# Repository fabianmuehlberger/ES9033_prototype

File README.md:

# ES9033_prototype
prototype board with ES9033 DAC

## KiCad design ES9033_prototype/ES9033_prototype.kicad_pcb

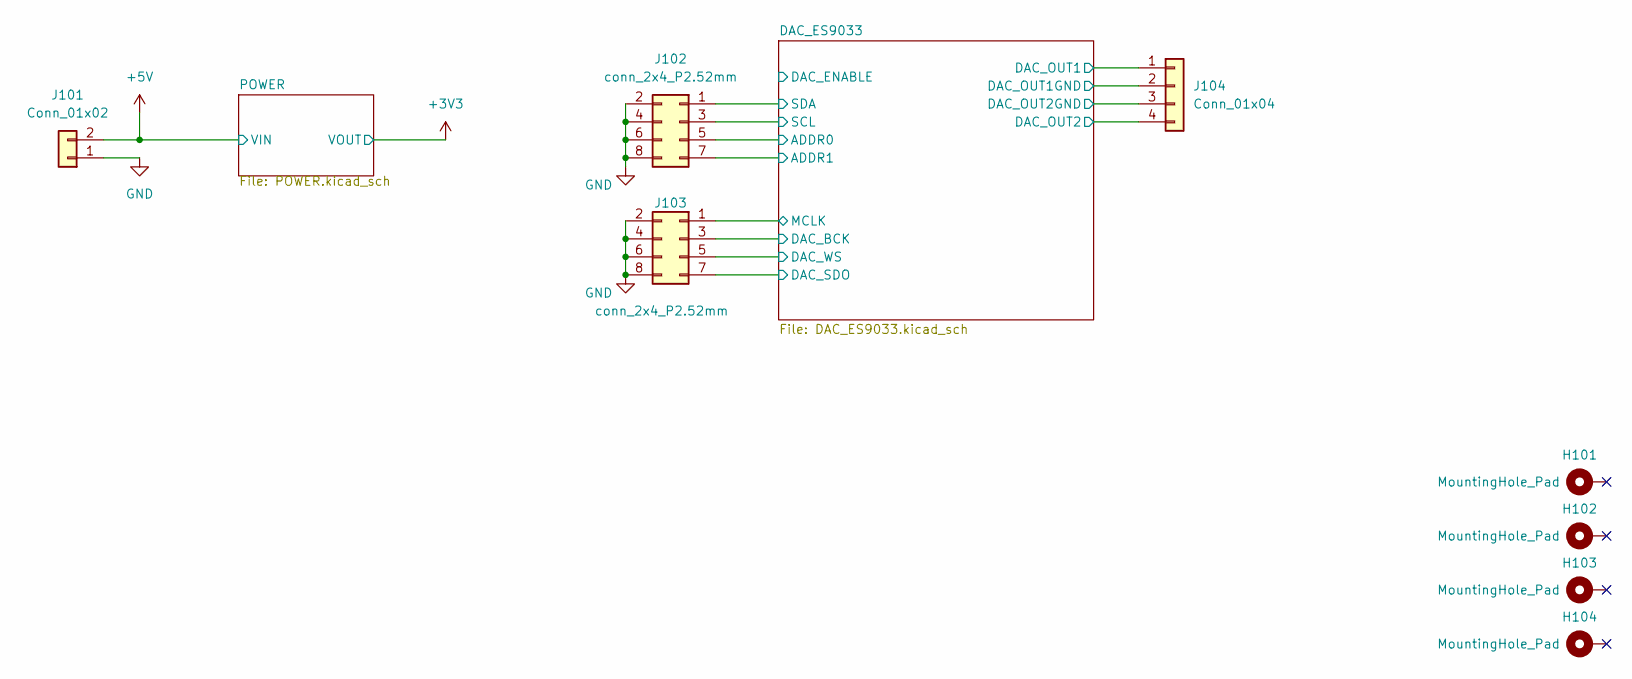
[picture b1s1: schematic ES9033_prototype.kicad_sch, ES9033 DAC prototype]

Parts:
H101, H102, H103, H104: MountingHole_Pad; MountingHole_3.2mm_M3_DIN965_Pad
J101: Conn_01x02; PinHeader_1x02_P2.54mm_Vertical
J102, J103: conn_2x4_P2.52mm; PinHeader_2x04_P2.54mm_Vertical
J104: Conn_01x04; PinHeader_1x04_P2.54mm_Vertical

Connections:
+5V: J101.2; also elsewhere on the board
/DAC_ES9033/ADDR0: J102.5; also elsewhere on the board
/DAC_ES9033/ADDR1: J102.7; also elsewhere on the board
/DAC_ES9033/DAC_BCK: J103.3; also elsewhere on the board
/DAC_ES9033/DAC_OUT1: J104.1; also elsewhere on the board
/DAC_ES9033/DAC_OUT2: J104.4; also elsewhere on the board
/DAC_ES9033/DAC_SDO: J103.7; also elsewhere on the board
/DAC_ES9033/DAC_WS: J103.5; also elsewhere on the board
/DAC_ES9033/MCLK: J103.1; also elsewhere on the board
/DAC_ES9033/SCL: J102.3; also elsewhere on the board
/DAC_ES9033/SDA: J102.1; also elsewhere on the board
GND: J101.1, J102.2, J102.4, J102.6, J102.8, J103.2, J103.4, J103.6, J103.8, J104.2, J104.3; also elsewhere on the board

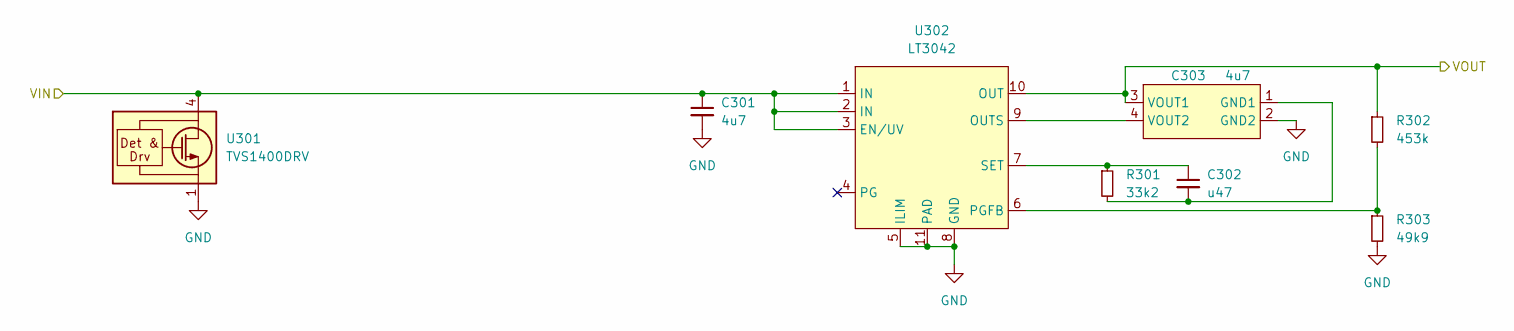
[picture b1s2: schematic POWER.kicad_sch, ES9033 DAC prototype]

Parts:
C301: 4u7; C_1206_3216Metric
C302: u47; C_1206_3216Metric
C303: 4u7; 1206_split
R301: 33k2; R_0805_2012Metric
R302: 453k; R_0805_2012Metric
R303: 49k9; R_0805_2012Metric
U301: TVS1400DRV; WSON-6-1EP_2x2mm_P0.65mm_EP1x1.6mm
U302: LT3042; DFN-10-1EP_3x3mm_P0.5mm_EP1.7x2.5mm

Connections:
+3V3: C303.3 (VOUT1), R302.1, U302.10 (OUT); also elsewhere on the board
+5V: C301.1, U301.4 (IN), U301.5 (IN), U301.6 (IN), U302.1 (IN), U302.2 (IN), U302.3 (EN/UV); also elsewhere on the board
GND: C301.2, C303.2 (GND2), R303.2, U301.1 (GND), U301.2 (GND), U301.3 (GND), U301.7 (GND), U302.5 (ILIM), U302.8 (GND), U302.11 (PAD); also elsewhere on the board
unnamed: C302.1, R301.1, U302.7 (SET)
unnamed: C302.2, C303.1 (GND1), R301.2
unnamed: C303.4 (VOUT2), U302.9 (OUTS)
unnamed: R302.2, R303.1, U302.6 (PGFB)

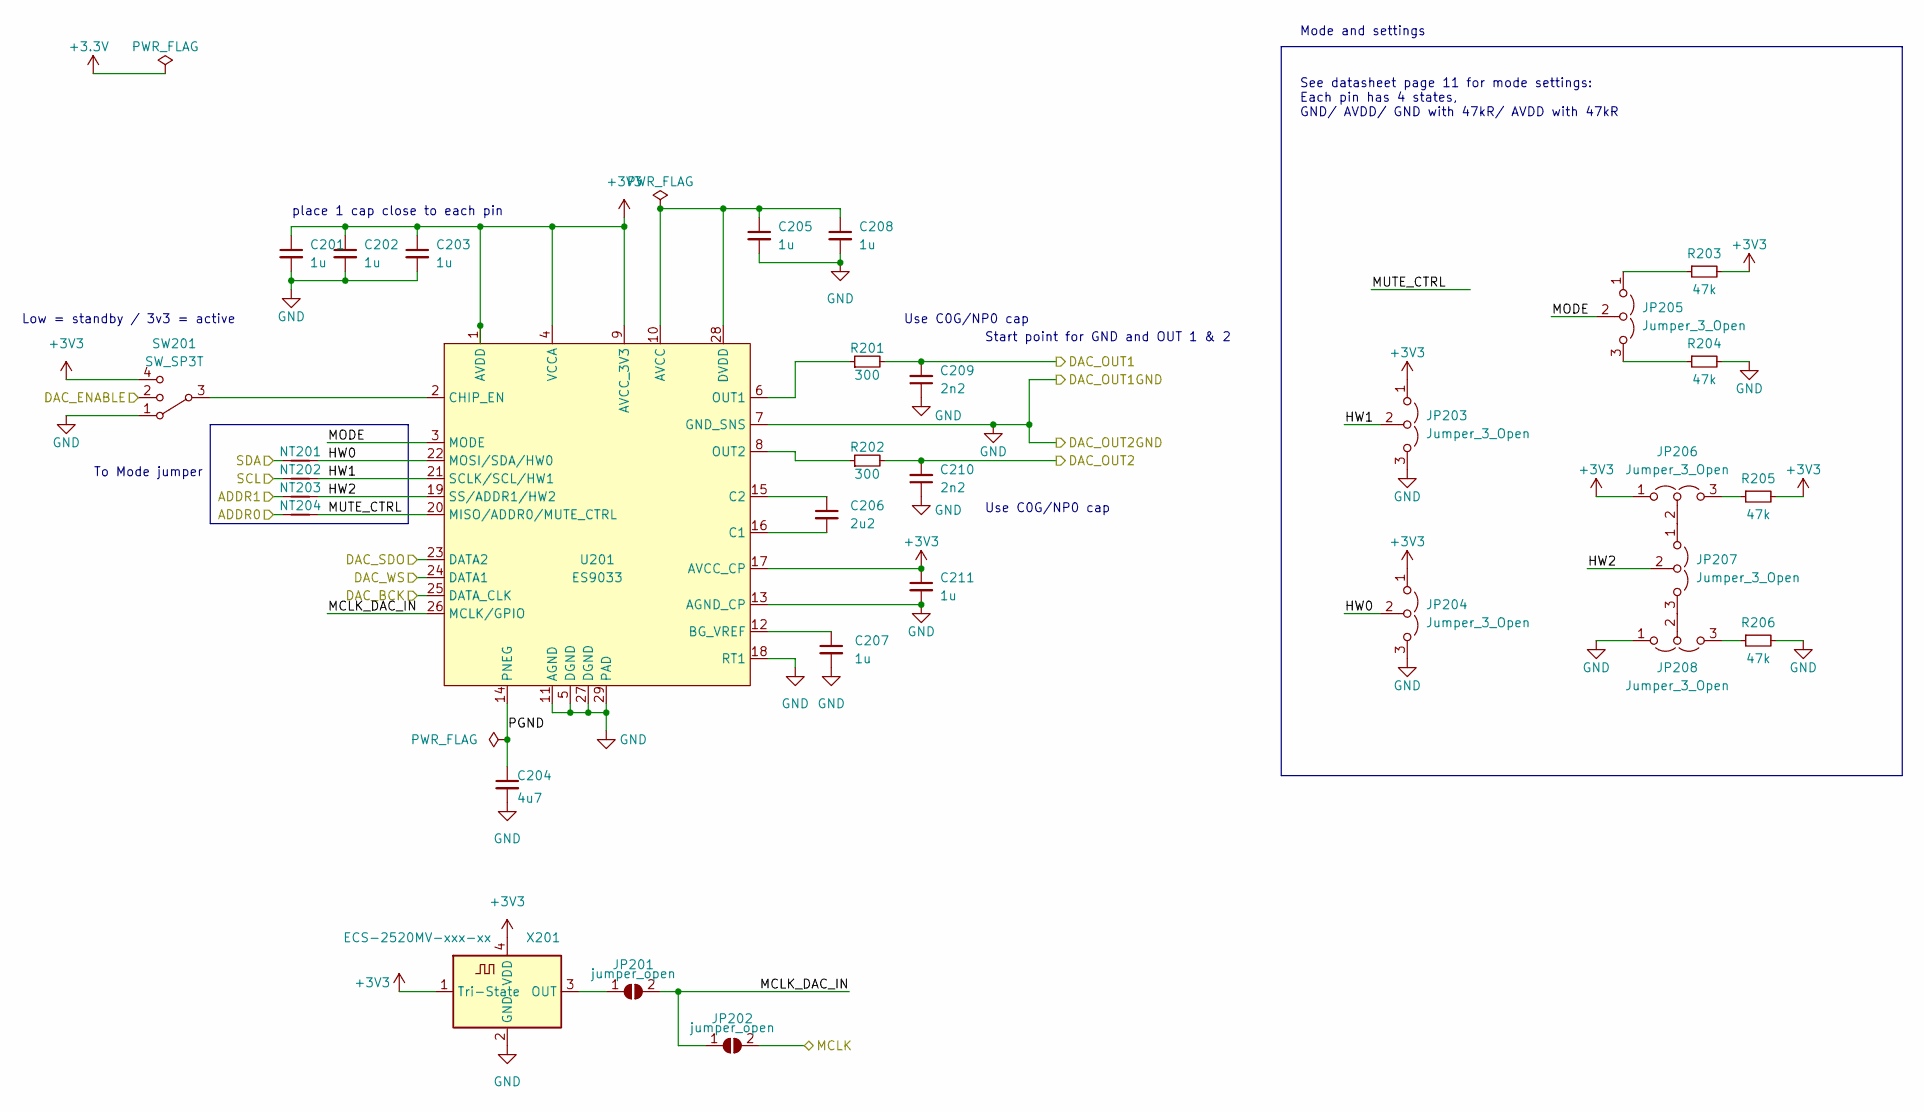
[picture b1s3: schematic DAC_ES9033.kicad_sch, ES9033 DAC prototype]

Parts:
C201, C202, C203, C205, C207, C208, C211: 1u; C_0805_2012Metric
C204: 4u7; C_0805_2012Metric
C206: 2u2; C_0805_2012Metric
C209, C210: 2n2; C_0805_2012Metric
JP201, JP202: jumper_open; SolderJumper-2_P1.3mm_Open_Pad1.0x1.5mm
JP203, JP204, JP205, JP206, JP207, JP208: Jumper_3_Open; PinHeader_1x03_P2.54mm_Vertical
NT201, NT202, NT203, NT204: NetTie_2; NetTie-2_SMD_Pad0.5mm
R201, R202: 300; R_0805_2012Metric
R203, R204, R205, R206: 47k; R_0805_2012Metric
SW201: SW_SP3T; SW_SP3T_PCM13
U201: ES9033; QFN-28-1EP_5x5mm_P0.5mm_EP3.35x3.35mm
X201: ECS-2520MV-xxx-xx; Oscillator_SMD_ECS_2520MV-xxx-xx-4Pin_2.5x2.0mm

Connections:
+3V3: C201.1, C202.1, C203.1, C211.1, JP203.1 (A), JP204.1 (A), JP206.1 (A), R203.2, R205.2, SW201.4, U201.1 (AVDD), U201.4 (VCCA), U201.9 (AVCC_3V3), U201.17 (AVCC_CP), X201.1 (Tri-State), X201.4 (VDD); also elsewhere on the board
/DAC_ES9033/ADDR0: NT204.1; also elsewhere on the board
/DAC_ES9033/ADDR1: NT203.1; also elsewhere on the board
/DAC_ES9033/DAC_BCK: U201.25 (DATA_CLK); also elsewhere on the board
/DAC_ES9033/DAC_ENABLE: SW201.2
/DAC_ES9033/DAC_OUT1: C209.2, R201.2; also elsewhere on the board
/DAC_ES9033/DAC_OUT2: C210.2, R202.2; also elsewhere on the board
/DAC_ES9033/DAC_SDO: U201.23 (DATA2); also elsewhere on the board
/DAC_ES9033/DAC_WS: U201.24 (DATA1); also elsewhere on the board
/DAC_ES9033/HW0: JP204.2 (C), NT201.2, U201.22 (MOSI/SDA/HW0)
/DAC_ES9033/HW1: JP203.2 (C), NT202.2, U201.21 (SCLK/SCL/HW1)
/DAC_ES9033/HW2: JP207.2 (C), NT203.2, U201.19 (SS/ADDR1/HW2)
/DAC_ES9033/MCLK: JP202.2 (B); also elsewhere on the board
/DAC_ES9033/MCLK_DAC_IN: JP201.2 (B), JP202.1 (A), U201.26 (MCLK/GPIO)
/DAC_ES9033/MODE: JP205.2 (C), U201.3 (MODE)
/DAC_ES9033/MUTE_CTRL: NT204.2, U201.20 (MISO/ADDR0/MUTE_CTRL)
/DAC_ES9033/PGND: C204.1, U201.14 (PNEG)
/DAC_ES9033/SCL: NT202.1; also elsewhere on the board
/DAC_ES9033/SDA: NT201.1; also elsewhere on the board
GND: C201.2, C202.2, C203.2, C204.2, C205.2, C207.2, C208.2, C209.1, C210.1, C211.2, JP203.3 (B), JP204.3 (B), JP208.1 (A), R204.2, R206.2, SW201.1, U201.5 (DGND), U201.7 (GND_SNS), U201.11 (AGND), U201.13 (AGND_CP), U201.18 (RT1), U201.27 (DGND), U201.29 (PAD), X201.2 (GND); also elsewhere on the board
unnamed: C205.1, C208.1, U201.10 (AVCC), U201.28 (DVDD)
unnamed: C206.1, U201.15 (C2)
unnamed: C206.2, U201.16 (C1)
unnamed: C207.1, U201.12 (BG_VREF)
unnamed: JP201.1 (A), X201.3 (OUT)
unnamed: JP205.1 (A), R203.1
unnamed: JP205.3 (B), R204.1
unnamed: JP206.2 (C), JP207.1 (A)
unnamed: JP206.3 (B), R205.1
unnamed: JP207.3 (B), JP208.2 (C)
unnamed: JP208.3 (B), R206.1
unnamed: R201.1, U201.6 (OUT1)
unnamed: R202.1, U201.8 (OUT2)
unnamed: SW201.3, U201.2 (CHIP_EN)

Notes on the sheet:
place 1 cap close to each pin
Mode and settings
To Mode jumper
Use C0G/NP0 cap
Start point for GND and OUT 1 & 2
Low = standby / 3v3 = active
See datasheet page 11 for mode settings: Each pin has 4 states, GND/ AVDD/ GND with 47kR/ AVDD with 47kR

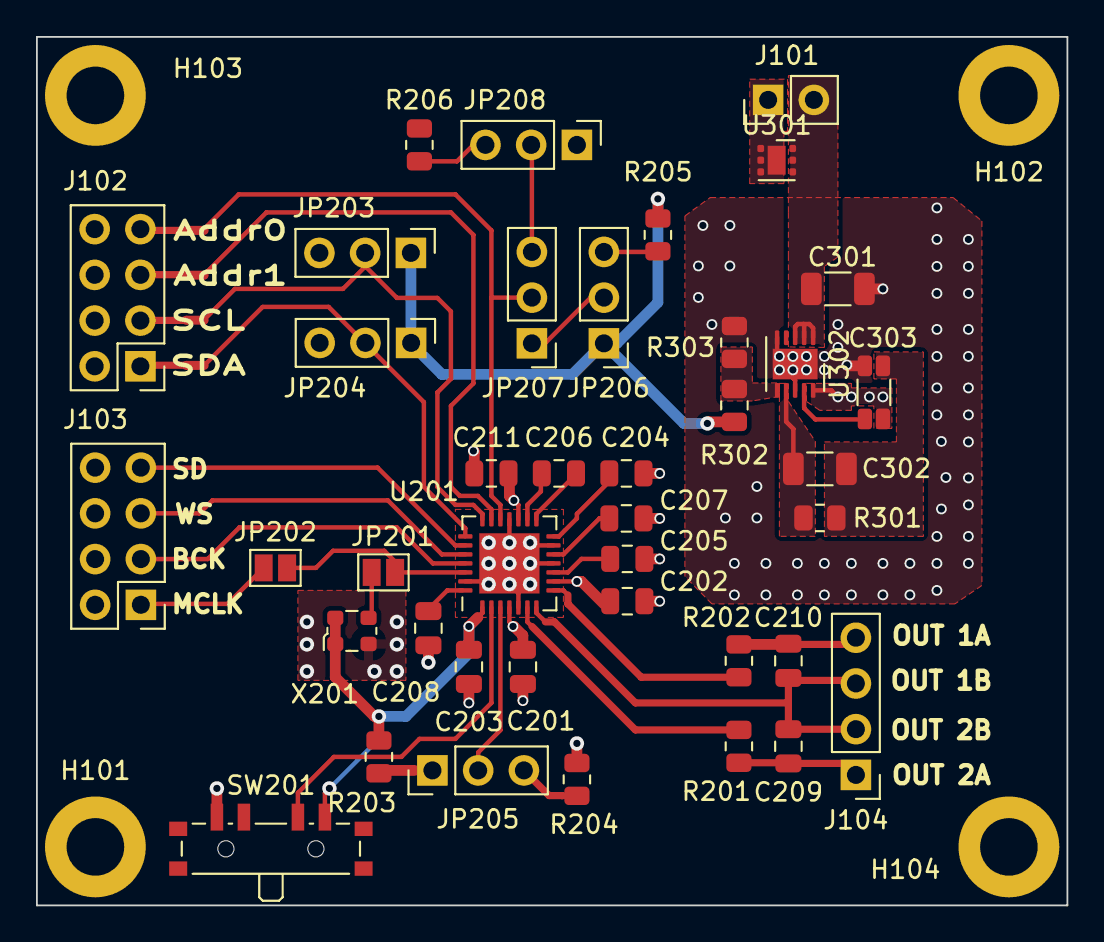
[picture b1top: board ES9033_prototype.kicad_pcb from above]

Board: 4 copper layers, 57.2 x 48.2 mm, 48 parts (0 on the bottom side), 38 nets.

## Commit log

2022-09-09 added Kicad Project
2022-09-09 added schematic title
2022-09-11 changed header
2022-09-11 update ignore
2022-09-11 changed header placement
2022-09-14 stuff
2022-10-03 removed grounding from mounting holes
